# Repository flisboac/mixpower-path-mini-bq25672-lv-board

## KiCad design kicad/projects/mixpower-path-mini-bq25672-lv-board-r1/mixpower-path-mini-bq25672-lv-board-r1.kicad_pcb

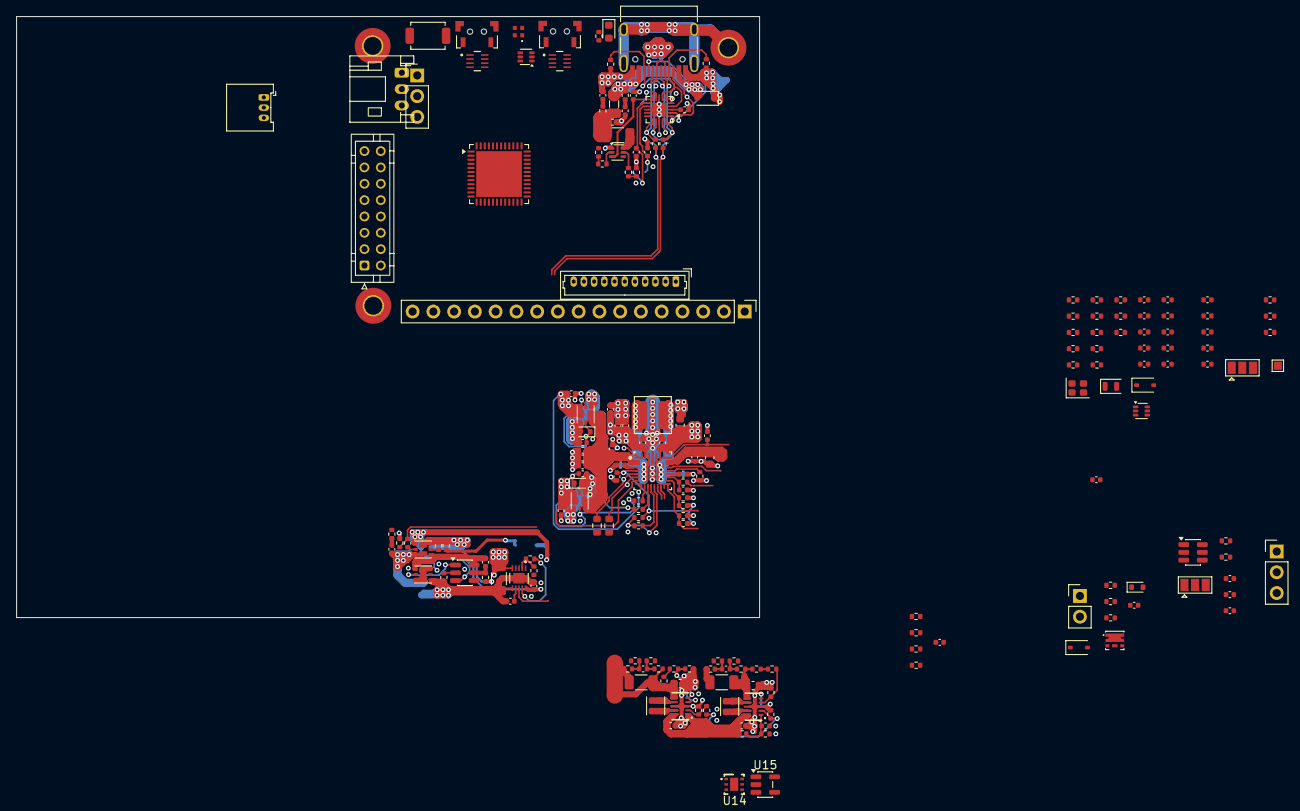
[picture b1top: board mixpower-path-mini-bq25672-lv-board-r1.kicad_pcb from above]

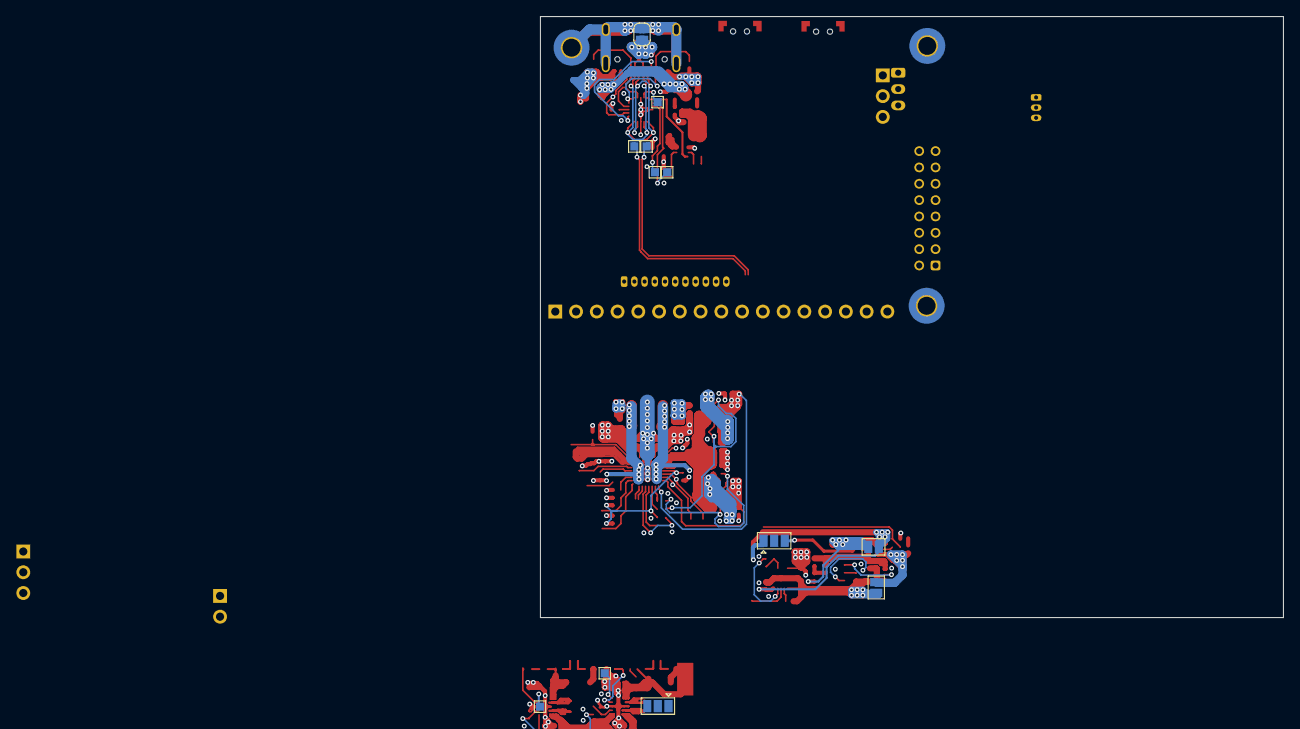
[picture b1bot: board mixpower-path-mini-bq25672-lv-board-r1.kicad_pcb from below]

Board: 4 copper layers, 90.9 x 73.6 mm, 205 parts (12 on the bottom side), 141 nets.

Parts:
C1: 1u; C_0402_1005Metric
C2: 10n; C_0402_1005Metric
C3, C4, C9, C10, C17, C18, C41, C42, C43, C44, C45, C46, C48, C49, C50, C61: 100n; C_0402_1005Metric
C5, C13, C16, C19, C20, C23, C24, C29, C30, C36, C37, C47, C51, C52, C53, C58, C60: 10u; C_0402_1005Metric
C6, C7: 330n; C_0402_1005Metric
C8, C11: 2.2u; C_0402_1005Metric
C12: 2.2u; R_0402_1005Metric
C14, C15, C21, C22: 100u; C_0402_1005Metric
C25, C26, C39, C40: 47u; C_0603_1608Metric
C27, C28, C34, C38: 1n; C_0402_1005Metric
C31, C32, C33, C35: 47n; C_0402_1005Metric
C54, C55: 7p; C_0402_1005Metric
C56, C57: 10p; C_0402_1005Metric
C59: 470p; C_0402_1005Metric
D1, D2: PESD24VV1BA; D_SOD-323
D3, D4, D5: BZX584C18; D_SOD-523
D6: RED_CHG; LED_0603_1608Metric
D7: 1N5817WS; D_SOD-323
D8: SK6805-EC14
FB1: BLM21PG300SN1D; L_0805_2012Metric
H1, H2, H3: M1; MountingHole_2.2mm_M2_Pad_TopBottom
J1: USB_C_Receptacle_HRO_TYPE-C-31-M-12
J2: BAT_HEADERS; PinHeader_1x03_P2.54mm_Vertical
J3: BATT_JST; JST_PH_S3B-PH-K_1x03_P2.00mm_Horizontal
J4: BATT_PB; Molex_PicoBlade_53048-0310_1x03_P1.25mm_Horizontal
J5: VEXT; PinHeader_1x02_P2.54mm_Vertical
J6: DATA_CONN; Molex_PicoBlade_53047-1110_1x11_P1.25mm_Vertical
J7: DATA_HEADER; PinHeader_1x17_P2.54mm_Vertical
J8: HAT; JST_PHD_B16B-PHDSS_2x08_P2.00mm_Vertical
J9: DEBUG; PinHeader_1x03_P2.54mm_Vertical
JP1: USB_GND_TO_SHIELD; SolderJumper-2_P1.3mm_Open_RoundedPad1.0x1.5mm
JP2, JP4: RTC; SolderJumper-3_P1.3mm_Open_Pad1.0x1.5mm
JP3: VCC_SEL; SolderJumper-3_P1.3mm_Open_Pad1.0x1.5mm
JP5: VDD1_SEL; SolderJumper-3_P1.3mm_Open_Pad1.0x1.5mm
JP9: SHIPFET_DIS; SolderJumper-2_P1.3mm_Open_Pad1.0x1.5mm
JP10: BPROT_DIS; SolderJumper-2_P1.3mm_Open_Pad1.0x1.5mm
L1: 1u; L_Coilcraft_XAL4020-XXX
L2, L3: 470n; L_Changjiang_FTC201612S
NT1: 3V3_TO_3V3LP; NetTie-2_SMD_Pad2.0mm
Q1, Q8: DMG1029SVQ; SOT-563
Q2, Q3, Q5, Q6: DMN3032LFDBQ; Diodes-Incorporated_U-DFN2020-6_Type-B
Q4: NTLJS17D0P03P8Z; vendor-onsemi-483av
Q7: Si1026X; SOT-563
R1, R2, R31: 5.1k; R_0402_1005Metric
R3, R4: 27; R_0402_1005Metric
R5, R6, R12, R22: 2; R_0402_1005Metric
R7, R10, R17, R27, R28: 220; R_0402_1005Metric
R8, R11, R20, R30, R77: 1M; R_0402_1005Metric
R9: 1.8k; R_1206_3216Metric
R13, R23, R34, R50, R51, R52, R53, R54, R55, R56, R57: 100k; R_0402_1005Metric
R14, R36: 100; R_0402_1005Metric
R15, R60, R76, R79: 1k; R_0402_1005Metric
R16, R19, R26, R37, R38, R41, R42, R45, R68, R69, R70, R71, R72, R73, R75: 0; R_0402_1005Metric
R18, R58, R59: 10k; R_0402_1005Metric
R21, R48, R49: 0.01; R_1206_3216Metric
R24, R25: 0; R_0603_1608Metric
R29: 2.2k; R_0402_1005Metric
R32: 30k; R_0402_1005Metric
R33: 127k; R_0402_1005Metric
R35: 3k; R_0402_1005Metric
R39, R40, R61, R64, R74: 10M; R_0402_1005Metric
R43: 806k; R_0402_1005Metric
R44, R47: 91k; R_0402_1005Metric
R46: 511k; R_0402_1005Metric
R62, R63, R65, R66, R67, R78: 4.7k; R_0402_1005Metric
SW1, SW3: TS-A002
SW2: TS-A002; SW_SPST_TS-1088-xR020
TP1: D+; TestPoint_Pad_1.0x1.0mm
TP2: D-; TestPoint_Pad_1.0x1.0mm
TP3: CC1; TestPoint_Pad_1.0x1.0mm
TP4: CC2; TestPoint_Pad_1.0x1.0mm
TP5: ~{USBC_FLT}; TestPoint_Pad_1.0x1.0mm
TP6: SOC_RST_PP; TestPoint_Pad_1.0x1.0mm
TP7: ~{5V_PG}; TestPoint_Pad_1.0x1.0mm
TP8: ~{3V3_PG}; TestPoint_Pad_1.0x1.0mm
U1: TPD8S300A; vendor-ti-RUK0020B
U2: FS312F-G; SOT-23-6
U3: MAX17055ETB; SPECIFIC_MAX17055ETB_21-100013A_T102A2&plus_1C_MXM
U4: BQ25672; vendor-ti-RQM0029A-MFG
U5, U6: TPS63802; vendor-ti-DLA0010A
U7, U8: RT9829GQW; Specific_DFN8_RT9829_RIT
U9: STM32G0B1CEU6; QFN-48-1EP_7x7mm_P0.5mm_EP5.6x5.6mm
U10: TPS22917DBV; SOT-23-6
U14: TPS7A2601; vendor-ti-DRV0006A-NoThermalVias
U15: RT9080-33GJ5; TSOT-23-5
Y1: X201232768KJD2SI; Crystal_SMD_2012-2Pin_2.0x1.2mm
Y2: X201624MKB4SI; Crystal_SMD_2016-4Pin_2.0x1.6mm

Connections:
/input-battery/BATP: JP2.3 (B), R16.1, R36.1
/input-battery/BPROT_CS: R15.1, U2.2 (CS)
/input-battery/BPROT_OC: Q3.5 (G2), U2.3 (OC)
/input-battery/BPROT_OD: Q3.2 (G1), U2.1 (OD)
/input-battery/BPROT_VCC: C9.1, R14.2, U2.5 (VCC)
/input-battery/FG_AIN: R18.2, R19.1, U3.2 (AIN)
/input-battery/FG_REG: C11.1, U3.7 (REG)
/input-battery/FG_THRM: R18.1, U3.9 (THRM)
/input-battery/SDRV: C34.1, R17.1, R20.1, U4.24 (SDRV)
/input-battery/SHIPFET_G: Q2.5 (G2), R17.2
/input-battery/VBAT_GND: C10.2, C11.2, JP10.2 (B), Q3.4 (S2), R15.2, R21.1, U3.6 (CSP), U3.11 (EPAD)
/input-battery/VBAT_GND_MID: Q3.3 (D2), Q3.6 (D1), Q3.7 (D1), Q3.8 (D2)
/input-battery/VBAT_GND_RPP: C9.2, Q2.1 (S1), Q3.1 (S1), U2.6 (GND)
/input-battery/VBAT_IN: J2.1, J3.1, J4.1, JP9.1 (A), Q2.3 (D2), Q2.8 (D2), R12.1, R13.1, R14.1, R16.2
/input-battery/VBAT_IN_GND: C8.2, J2.2, J3.2, J4.2, JP10.1 (A), Q2.6 (D1), Q2.7 (D1)
/input-battery/VBAT_IN_P: C8.1, R12.2
/input-battery/VBAT_IN_RPP_G: Q2.2 (G1), R13.2
/input-battery/~IRQ: J8.8, U3.8 (ALRT), U4.21 (~INT), U9.1 (PC13)
/input-usb/DISCH: R10.2, R11.1, U9.25 (PB13)
/input-usb/DISCH_DRAIN: Q1.6 (D1), R9.2
/input-usb/DISCH_G: Q1.2 (G1), R10.1
/input-usb/SHIELD: H1.1 (1_1), H2.1 (1_1), H3.1 (1_1), J1.S1 (SHIELD), JP1.2 (B)
/input-usb/USBC_CC1: J1.A5 (CC1), R2.1, U1.4 (C_CC1), U1.7 (RPD_G1)
/input-usb/USBC_CC2: J1.B5 (CC2), R1.1, U1.5 (C_CC2), U1.6 (RPD_G2)
/input-usb/USBC_D+: J1.A6 (D+), J1.B6 (D+), R4.1, U1.16 (D4), U1.19 (D2)
/input-usb/USBC_D-: J1.A7 (D-), J1.B7 (D-), R3.1, U1.17 (D3), U1.20 (D1)
/input-usb/USBC_SBU1: J1.A8 (SBU1), U1.1 (C_SBU1)
/input-usb/USBC_SBU2: J1.B8 (SBU2), U1.2 (C_SBU2)
/input-usb/USBC_TPS_VCC: C1.1, Q1.3 (D2), U1.10 (VPWR)
/input-usb/USBP_VBIAS: C3.1, U1.3 (VBIAS)
/input-usb/VBUS: C5.1, C18.2, FB1.2, J7.13, Q6.6 (D1), Q6.7 (D1), R6.1, R9.1, U4.8 (VAC2)
/input-usb/VBUS_USBC_IN: D1.2 (A2), FB1.1, J1.A4 (VBUS), J1.A9 (VBUS), J1.B4 (VBUS), J1.B9 (VBUS), R5.1
/input-usb/VBUS_USBC_IN_POST_P: C4.1, R6.2
/input-usb/VBUS_USBC_IN_PRE_P: C2.1, R5.2
/input-usb/VCC_DIS: R7.1, R8.1, U9.24 (PB12)
/input-usb/~FLT: TP5.1 (1_1), U1.9 (~FLT), U9.31 (PC7)
/input-vext/VEXT: C13.1, C17.1, D3.1 (K), Q4.4 (S), Q4.8 (S), Q5.6 (D1), Q5.7 (D1), U4.9 (VAC1)
/input-vext/VEXT_FLT_P: C12.1, R22.2
/input-vext/VEXT_G: D3.2 (A), Q4.3 (G), R23.1
/input-vext/VEXT_IN: D2.2 (A2), J5.1, Q4.1 (D), Q4.2 (D), Q4.5 (D), Q4.6 (D), Q4.7 (D), R22.1
/output-headers/3V3: J6.5, J7.5, J8.16, JP3.1 (A), JP5.1 (A), R49.2, R52.2
/output-headers/5V: J6.11, J7.11, J8.1, JP3.3 (B), JP5.3 (B), Q8.4 (S2), R48.2, R51.2, R77.1
/output-headers/BOOT: J6.10, J7.10, JP4.2 (C)
/output-headers/D+: J6.8, J7.8, R4.2, R24.2, TP2.1 (1_1), U9.34 (PA10/PA12)
/output-headers/D-: J6.9, J7.9, R3.2, R25.2, TP1.1 (1_1), U9.33 (PA9/PA11)
/output-headers/GP1_IRQ2: J8.12, U9.11 (PA0)
/output-headers/GP2: J8.7, U9.12 (PA1)
/output-headers/GP3: J8.14, U9.15 (PA4)
/output-headers/GP4: J8.5, U9.16 (PA5)
/output-headers/PHER2_MISO_SDA: J8.9, U9.43 (PB4)
/output-headers/PHER2_SCK: J8.6, U9.42 (PB3)
/output-headers/SWDIO: J9.1, U9.35 (PA13)
/output-headers/USER1_SCL_TX: J6.1, J7.1, J8.15, R63.2, U9.45 (PB6)
/output-headers/USER1_SDA_RX: J6.3, J7.3, J8.2, R62.2, U9.46 (PB7)
/output-headers/VDD1: C60.1, J7.12, R75.2, U10.6 (VOUT)
/output-headers/~BTN: C45.1, J6.6, J7.6, R26.2, R58.2, SW1.2, U7.3 (~SR1), U9.47 (PB8)
/output-headers/~IRQB: D7.2 (A), J6.4, J7.4, R67.2, U9.14 (PA3)
/output-headers/~RST: C46.1, J6.7, J7.7, J8.3, R59.2, SW2.2, U7.4 (~RST1), U8.3 (~SR1), U9.10 (PF2)
/power-path/BC_BATP: C35.1, R36.2, U4.18 (BATP)
/power-path/BC_BTST1: C32.1, U4.4 (BTST1)
/power-path/BC_BTST2: C33.1, U4.19 (BTST2)
/power-path/BC_D+: R24.1, U4.6 (D+)
/power-path/BC_D-: R25.1, U4.7 (D-)
/power-path/BC_ILIM: R33.1, R34.2, U4.17 (ILIM_HIZ)
/power-path/BC_PROG: R35.2, U4.20 (PROG)
/power-path/TS: J2.3, J3.3, J4.3, R19.2, R31.1, R32.2, U4.16 (TS)
/power-path/VAC1_MID: C27.1, D4.2 (A), Q5.1 (S1), Q5.4 (S2)
/power-path/VAC2_MID: C28.2, D5.2 (A), Q6.1 (S1), Q6.4 (S2)
/power-path/VBAT: C10.1, C22.1, C26.1, J7.16, JP2.1 (A), JP9.2 (B), Q2.4 (S2), U3.10 (BATT), U4.22 (BAT), U4.23 (BAT)
/power-path/VIN1_ACDRV_G: R27.2, U4.11 (ACDRV1)
/power-path/VIN1_G: C27.2, D4.1 (K), Q5.2 (G1), Q5.5 (G2), R27.1
/power-path/VIN2_ACDRV_G: R28.2, U4.10 (ACDRV2)
/power-path/VIN2_G: C28.1, D5.1 (K), Q6.2 (G1), Q6.5 (G2), R28.1
/power-path/VOTG: C15.1, C20.1, C24.1, C30.1, J7.15, U4.29 (PMID)
/power-path/VREGNLP: C16.1, R29.2, R30.2, R31.2, R33.2, U4.5 (REGN)
/power-path/VSEL: C14.1, C19.1, C23.1, C29.1, Q5.3 (D2), Q5.8 (D2), Q6.3 (D2), Q6.8 (D2), U4.2 (VBUS), U4.3 (VBUS)
/power-path/VSWN_SW1: C32.2, L1.1, U4.28 (SW1)
/power-path/VSWN_SW2: C33.2, L1.2, U4.26 (SW2)
/power-path/VSYS: C21.1, C25.1, C36.1, C37.1, J7.14, R39.2, U4.25 (SYS), U5.10 (VIN), U6.1 (EN), U6.10 (VIN)
/power-path/~BC_QON: R26.1, U4.12 (~QON)
/power-path/~CE: C31.1, R30.1, U4.13 (~CE), U9.39 (PD1)
/power-path/~STAT: D6.1 (K), U4.1 (STAT)
/soc-control/3V3LP: C50.1, C53.1, NT1.1, Q1.4 (S2), U9.6 (VDD)
/soc-control/5V_EN: R37.2, U9.41 (PD3)
/soc-control/BOOT: C47.1, JP4.1 (A), R60.2, R72.2, SW3.2
/soc-control/FRSTX1: Q7.2 (G), R61.1, U9.26 (PB14)
/soc-control/FRSTX2: Q7.5 (G), R64.1, U9.30 (PC6)
/soc-control/IRQB_TX: D7.1 (K), U9.13 (PA2)
/soc-control/OSC32_IN: R68.2, U9.2 (PC14)
/soc-control/OSC32_OUT: R69.2, U9.3 (PC15)
/soc-control/OSC_IN: R70.1, U9.8 (PF0)
/soc-control/OSC_OUT: R71.2, U9.9 (PF1)
/soc-control/PHER1_SCL: J8.13, R66.2, U3.3 (SCL), U4.14 (SCL), U9.18 (PA7)
/soc-control/PHER1_SDA: J8.4, R65.2, U3.4 (SDA), U4.15 (SDA), U9.17 (PA6)
/soc-control/PHER2_MOSI_SCL: J8.11, R73.1, U9.44 (PB5)
/soc-control/PHER2_RGB_CS: Q8.2 (G1), R78.1, U9.37 (PA15)
/soc-control/PHER2_RGB_DO: Q8.1 (S1), R73.2, R78.2
/soc-control/SNS_3V3_N: C42.1, R52.1, R56.1, U9.20 (PB1)
/soc-control/SNS_3V3_P: C42.2, R53.1, R57.1, U9.19 (PB0)
/soc-control/SNS_5V_N: C41.2, R51.1, R55.1, U9.22 (PB10)
/soc-control/SNS_5V_P: C41.1, R50.1, R54.1, U9.21 (PB2)
/soc-control/SWCLK: J9.3, R72.1, U9.36 (PA14)
/soc-control/SWREG_MODE: R38.2, R40.2, U5.2 (MODE), U9.40 (PD2)
/soc-control/USBC_CC1: C6.1, Q7.6 (D), TP3.1 (1_1), U1.12 (CC1), U9.28 (PA8), U9.29 (PA9/UCPD1_DBCC1)
/soc-control/USBC_CC2: C7.1, Q7.3 (D), TP4.1 (1_1), U1.11 (CC2), U9.27 (PB15), U9.32 (PA10/UCPD1_DBCC2)
/soc-control/VBAT: C48.1, C51.1, JP2.2 (C), U9.4 (VBAT)
/soc-control/VDD1_EN: R74.1, U9.48 (PB9), U10.3 (ON)
/soc-control/VREF: C49.1, C52.1, U9.5 (VREF+)
/soc-control/~PHER2_RGB_EN: R76.2, U9.38 (PD0)
/soc-vreg/3V3_PRE: C40.1, NT1.2, R45.2, R49.1, R53.2, U6.6 (VOUT)
/soc-vreg/5V_PRE: C39.1, R42.2, R48.1, R50.2, U5.6 (VOUT)
/soc-vreg/VSWN_3V3_L1: L3.1, U6.9 (L1)
/soc-vreg/VSWN_3V3_L2: L3.2, U6.7 (L2)
/soc-vreg/VSWN_5V_L1: L2.1, U5.9 (L1)
/soc-vreg/VSWN_5V_L2: L2.2, U5.7 (L2)
/soc-vreg/VSWREG_3V3_FB: R46.1, R47.2, U6.4 (FB)
/soc-vreg/VSWREG_3V3_MODE: R38.1, R41.2, U6.2 (MODE)
/soc-vreg/VSWREG_3V3_PG: TP8.1 (1_1), U6.5 (PG)
/soc-vreg/VSWREG_5V_EN: C38.1, R37.1, R39.1, U5.1 (EN)
/soc-vreg/VSWREG_5V_FB: R43.1, R44.2, U5.4 (FB)
/soc-vreg/VSWREG_5V_PG: TP7.1 (1_1), U5.5 (PG)
/soc-vreg/~SNS_EN: R54.2, R55.2, R56.2, R57.2, U9.23 (PB11)
/util-buttons/SRST_BOOT_RST1: JP4.3 (B), U8.4 (~RST1)
/util-buttons/SRST_BOOT_RST2: R60.1, U8.1 (RST2)
/util-buttons/SRST_RST_RST2: TP6.1 (1_1), U7.1 (RST2)
/util-buttons/VPULLUP: C43.1, C44.1, JP3.2 (C), R58.1, R59.1, R62.1, R63.1, R65.1, R66.1, R67.1, SW3.1, U7.8 (VCC), U8.8 (VCC)
/util-rgb/EN_G: Q8.5 (G2), R76.1, R77.2
/util-rgb/VIN_RGB_LP: C61.1, D8.1 (VDD), Q8.3 (D2), R79.1
/vpath-vdd1/VDD1_CT_G: C59.2, U10.4 (CT)
/vpath-vdd1/VDD1_IN: C58.1, C59.1, JP5.2 (C), U10.1 (VIN)
/vpath-vdd1/VDD1_QOD_G: R75.1, U10.5 (QOD)
GND: C1.2, C2.2, C3.2, C4.2, C5.2, C6.2, C7.2, C12.2, C13.2, C14.2, C15.2, C16.2, C17.2, C18.1, C19.2, C20.2, C21.2, C22.2, C23.2, C24.2, C25.2, C26.2, C29.2, C30.2, C31.2, C34.2, C35.2, C36.2, C37.2, C38.2, C39.2, C40.2, C43.2, C44.2, C45.2, C46.2, C47.2, C48.2, C49.2, C50.2, C51.2, C52.2, C53.2, C54.1, C55.2, C56.1, C57.2, C58.2, C60.2, C61.2, D1.1 (A1), D2.1 (A1), D8.3 (GND), J1.A1 (GND), J1.A12 (GND), J1.B1 (GND), J1.B12 (GND), J5.2, J6.2, J7.2, J7.17, J8.10, J9.2, JP1.1 (A), Q1.1 (S1), Q7.1 (S), Q7.4 (S), R1.2, R2.2, R8.2, R11.2, R20.2, R21.2, R23.2, R32.1, R34.1, R35.1, R40.1, R41.1, R44.1, R47.1, R61.2, R64.2, R74.2, SW1.1, SW2.1, U1.8 (GND), U1.13 (GND), U1.18 (GND), U1.21 (GND), U3.5 (CSN), U4.27 (GND), U5.3 (AGND), U5.8 (GND), U6.3 (AGND), U6.8 (GND), U7.2 (VSS), U7.5 (DSR), U7.7 (~SR0), U8.2 (VSS), U8.5 (DSR), U8.7 (~SR0), U9.7 (VSS), U9.49 (VSS), U10.2 (GND), Y2.2 (G), Y2.4 (G)
unnamed: C54.2, R68.1, Y1.2
unnamed: C55.1, R69.1, Y1.1
unnamed: C56.2, R70.2, Y2.1
unnamed: C57.1, R71.1, Y2.3
unnamed: D6.2 (A), R29.1
unnamed: D8.4 (DI), Q8.6 (D1), R79.2
unnamed: Q1.5 (G2), R7.2
unnamed: R42.1, R43.2
unnamed: R45.1, R46.2

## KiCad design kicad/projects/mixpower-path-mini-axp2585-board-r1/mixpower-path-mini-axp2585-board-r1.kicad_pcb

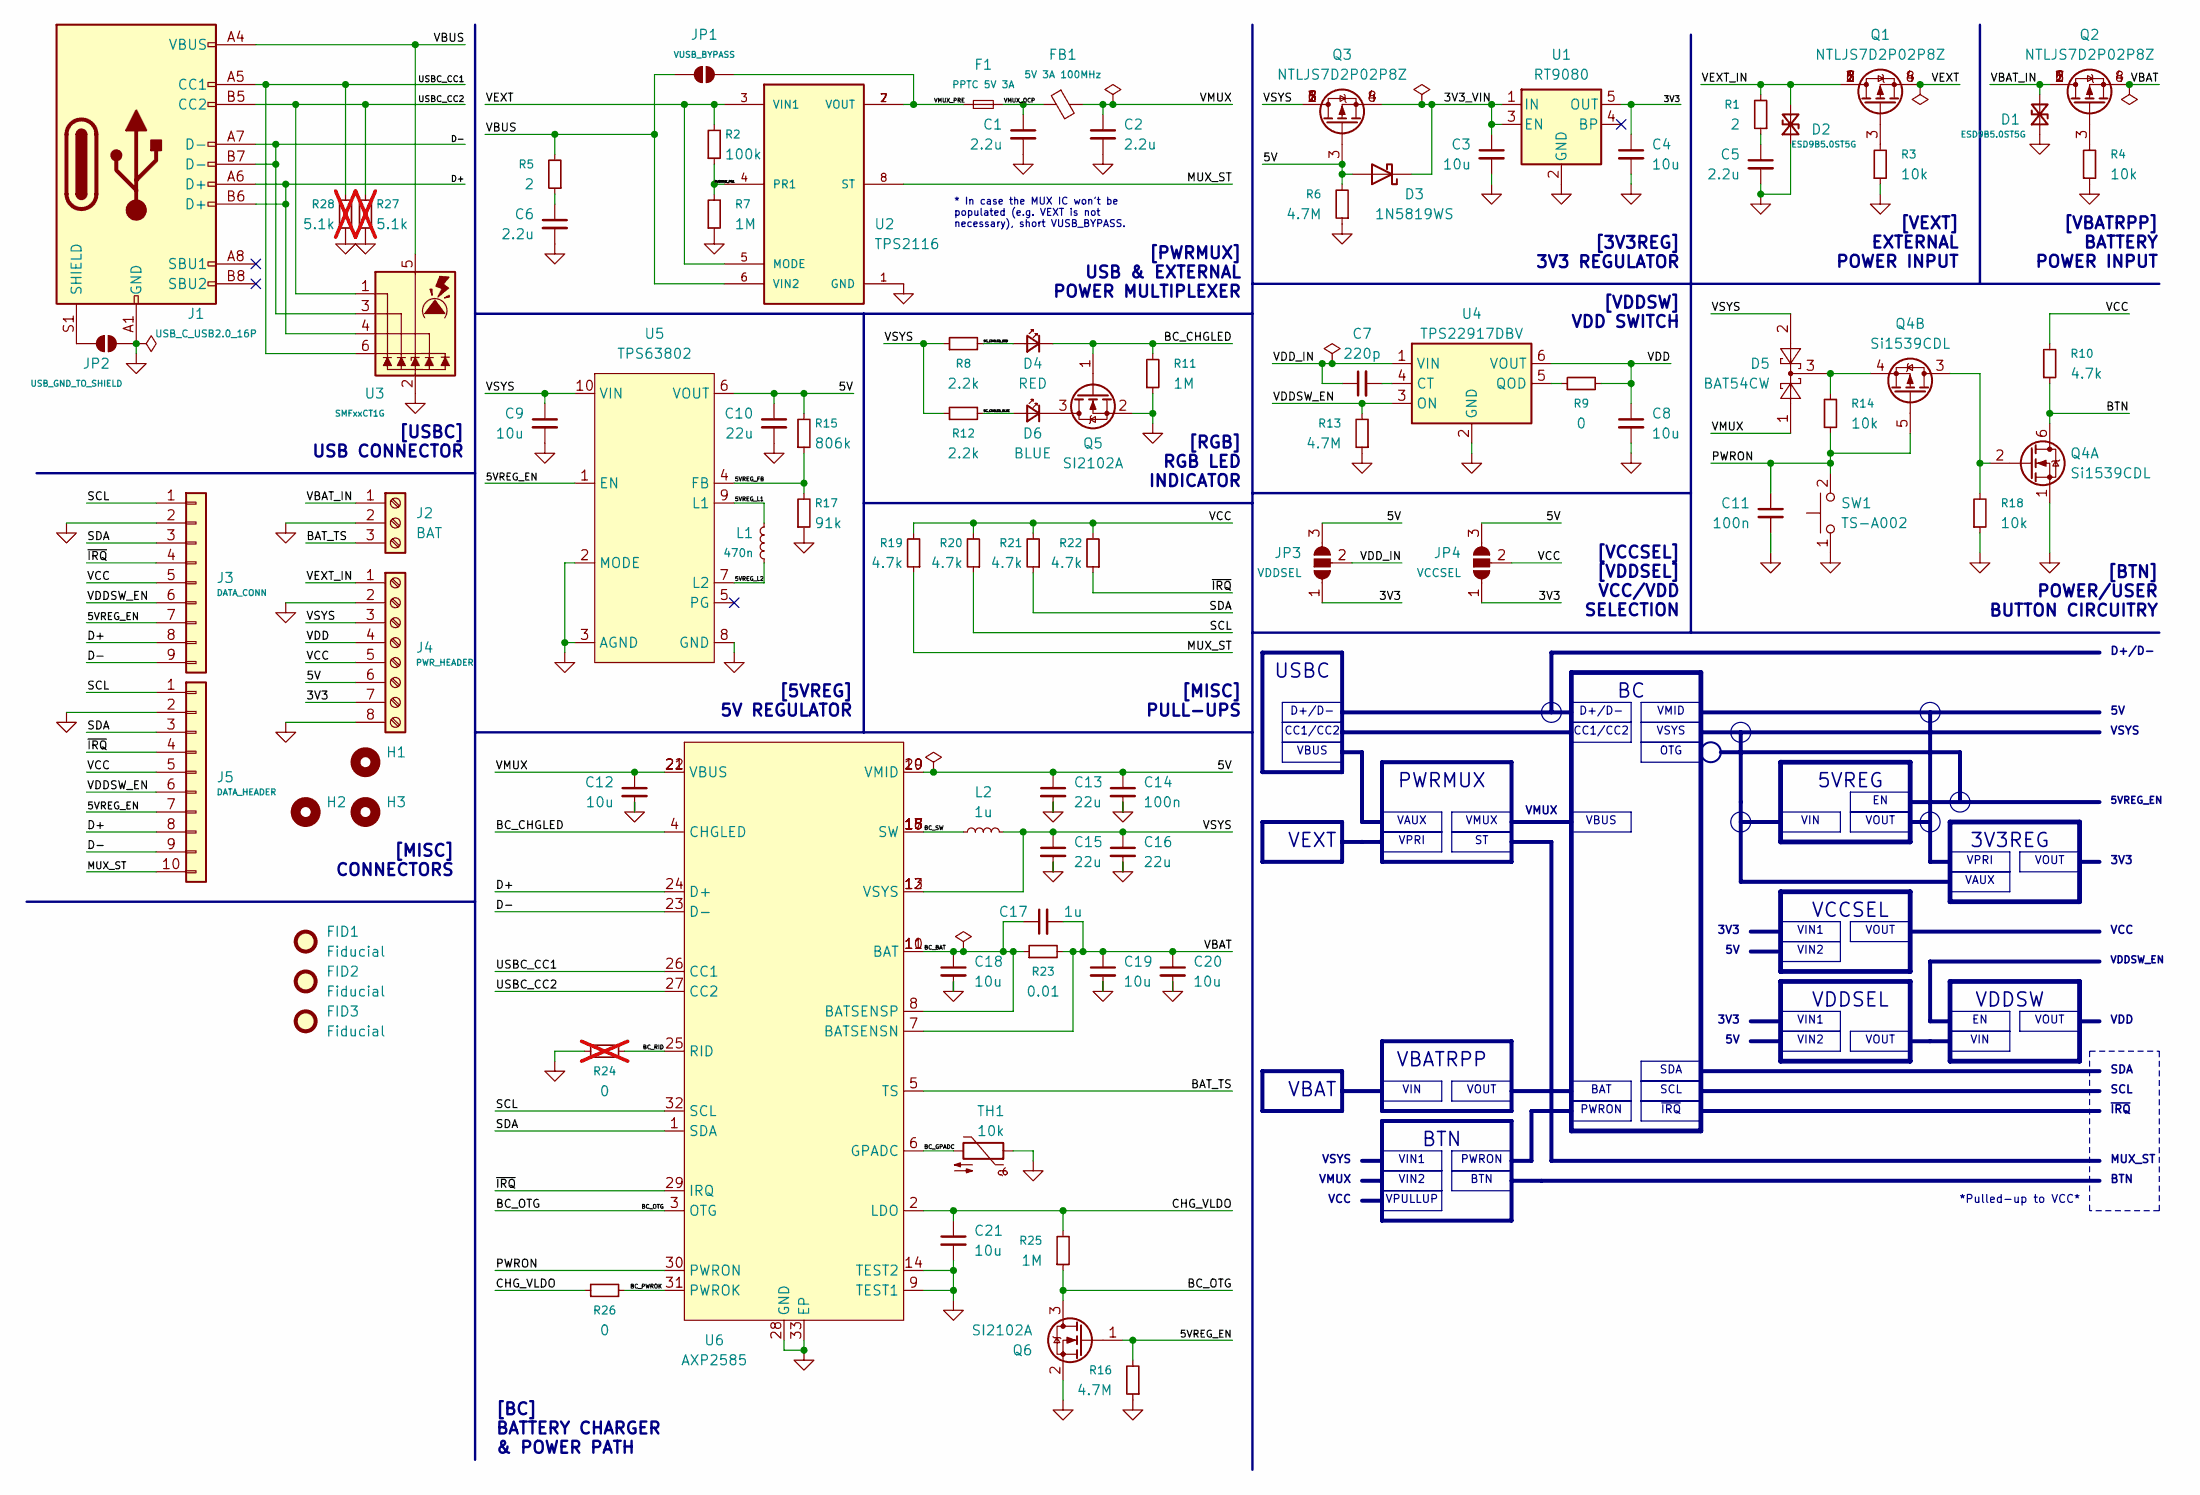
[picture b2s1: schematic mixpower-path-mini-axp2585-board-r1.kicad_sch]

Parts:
C1, C2, C5, C6: 2.2u; C_0402_1005Metric
C3, C4, C8, C12, C18, C19, C20, C21: 10u; C_0402_1005Metric
C7: 220p; C_0402_1005Metric
C9: 10u; C_0603_1608Metric
C10, C13, C15, C16: 22u; C_0603_1608Metric
C11, C14: 100n; C_0402_1005Metric
C17: 1u; C_0402_1005Metric
D1, D2: ESD9B5.0ST5G; D_SOD-923
D3: 1N5819WS; D_SOD-323
D4: RED; LED_0603_1608Metric
D5: BAT54CW; SOT-323_SC-70
D6: BLUE; LED_0603_1608Metric
F1: PPTC 5V 3A; Fuse_1210_3225Metric
FB1: 5V 3A 100MHz; L_1210_3225Metric
FID1, FID2, FID3: Fiducial; Fiducial_0.5mm_Mask1mm
H1, H2, H3: MountingHole; MountingHole_2.2mm_M2
J1: USB_C_USB2.0_16P; USB_C_Receptacle_HRO_TYPE-C-31-M-12
J2: BAT; JST_PH_S3B-PH-K_1x03_P2.00mm_Horizontal
J3: DATA_CONN; JST_ZH_B9B-ZR_1x09_P1.50mm_Vertical
J4: PWR_HEADER; PinHeader_1x08_P2.54mm_Vertical
J5: DATA_HEADER; PinHeader_1x10_P2.54mm_Vertical
JP1: VUSB_BYPASS; SolderJumper-2_P1.3mm_Open_RoundedPad1.0x1.5mm
JP2: USB_GND_TO_SHIELD; SolderJumper-2_P1.3mm_Open_RoundedPad1.0x1.5mm
JP3: VDDSEL; SolderJumper-3_P1.3mm_Open_RoundedPad1.0x1.5mm
JP4: VCCSEL; SolderJumper-3_P1.3mm_Open_RoundedPad1.0x1.5mm
L1: 470n; L_Coilcraft_XxL4020
L2: 1u; L_Coilcraft_XAL4020-XXX
Q1, Q2, Q3: NTLJS7D2P02P8Z; vendor-onsemi-483av
Q4: Si1539CDL; SOT-363_SC-70-6
Q5, Q6: SI2102A; SOT-323_SC-70
R1, R5: 2; R_0402_1005Metric
R2: 100k; R_0402_1005Metric
R3, R4, R14, R18: 10k; R_0402_1005Metric
R6, R13, R16: 4.7M; R_0402_1005Metric
R7, R11, R25: 1M; R_0402_1005Metric
R8, R12: 2.2k; R_0402_1005Metric
R9, R26: 0; R_0402_1005Metric
R10, R19, R20, R21, R22: 4.7k; R_0402_1005Metric
R15: 806k; R_0402_1005Metric
R17: 91k; R_0402_1005Metric
R23: 0.01; R_1210_3225Metric
R24: 0; R_0402_1005Metric; not fitted
R27, R28: 5.1k; R_0402_1005Metric; not fitted
SW1: TS-A002
TH1: 10k; R_0603_1608Metric
U1: RT9080; SOT-23-5
U2: TPS2116
U3: SMFxxCT1G; SOT-363_SC-70-6
U4: TPS22917DBV; SOT-23-6
U5: TPS63802; vendor-ti-DLA0010A
U6: AXP2585; QFN-32-1EP_5x5mm_P0.4mm_EP3x3mm; LCSC C20199912

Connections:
/3V3: C4.1, J4.7, JP3.1 (A), JP4.1 (A), U1.5 (OUT)
/3V3_VIN: C3.1, D3.1 (K), Q3.4 (S), Q3.8 (S), U1.1 (IN), U1.3 (EN)
/5V: C10.1, C13.1, C14.1, D3.2 (A), J4.6, JP3.3 (B), JP4.3 (B), Q3.3 (G), R6.2, R15.2, U5.6 (VOUT), U6.19 (VMID), U6.20 (VMID)
/5VREG_EN: J2.7, J3.7, J5.7, Q6.1 (G), R16.2, U5.1 (EN)
/5VREG_FB: R15.1, R17.2, U5.4 (FB)
/5VREG_L1: L1.1, U5.9 (L1)
/5VREG_L2: L1.2, U5.7 (L2)
/BC_BAT: C17.1, C18.1, R23.1, U6.8 (BATSENSP), U6.10 (BAT), U6.11 (BAT)
/BC_CHGLED: D4.1 (K), Q5.1 (G), R11.2, U6.4 (CHGLED)
/BC_CHGLED_BLUE: D6.2 (A), R12.2
/BC_CHGLED_RED: D4.2 (A), R8.2
/BC_GPADC: TH1.2, U6.6 (GPADC)
/BC_OTG: Q6.3 (D), R25.1, U6.3 (OTG)
/BC_PWROK: R26.2, U6.31 (PWROK)
/BC_RID: R24.2, U6.25 (RID)
/BC_SW: L2.1, U6.15 (SW), U6.16 (SW), U6.17 (SW), U6.18 (SW)
/BTN: Q4.6 (D1), R10.1
/CHG_VLDO: C21.1, R25.2, R26.1, U6.2 (LDO)
/D+: J1.A6 (D+), J1.B6 (D+), J2.8, J3.8, J5.8, U3.4 (I/O3), U6.24 (D+)
/D-: J1.A7 (D-), J1.B7 (D-), J2.9, J3.9, J5.9, U3.3 (I/O2), U6.23 (D-)
/MUX_ST: J2.10, J5.10, R19.1, U2.8 (ST)
/PWRMUX_PR1: R2.1, R7.2, U2.4 (PR1)
/PWRON: C11.1, Q4.5 (G2), R14.1, SW1.2, U6.30 (PWRON)
/USBC_CC1: J1.A5 (CC1), R28.2, U3.6 (I/O4), U6.26 (CC1)
/USBC_CC2: J1.B5 (CC2), R27.2, U3.1 (I/O1), U6.27 (CC2)
/VBAT: C17.2, C19.1, C20.1, Q2.4 (S), Q2.8 (S), R23.2, U6.7 (BATSENSN)
/VBUS: J1.A4 (VBUS), J1.A9 (VBUS), J1.B4 (VBUS), J1.B9 (VBUS), JP1.2 (B), R5.2, U2.6 (VIN2), U3.5 (I/O5)
/VCC: J2.5, J3.5, J4.5, J5.5, JP4.2 (C), R10.2, R19.2, R20.2, R21.2, R22.2
/VDD: C8.1, J4.4, R9.2, U4.6 (VOUT)
/VDDSW_EN: J2.6, J3.6, J5.6, R13.2, U4.3 (ON)
/VDD_IN: C7.1, JP3.2 (C), U4.1 (VIN)
/VEXT: Q1.4 (S), Q1.8 (S), R2.2, U2.3 (VIN1), U2.5 (MODE)
/VEXT_IN: D2.2 (A2), J4.1, Q1.1 (D), Q1.2 (D), Q1.5 (D), Q1.6 (D), Q1.7 (D), R1.2
/VMUX: C2.1, C12.1, D5.1 (A1), FB1.2, U6.21 (VBUS), U6.22 (VBUS)
/VMUX_OCP: C1.1, F1.2, FB1.1
/VMUX_PRE: F1.1, JP1.1 (A), U2.2 (VOUT), U2.7 (VOUT)
/VSYS: C9.1, C15.1, C16.1, D5.2 (A2), J4.3, L2.2, Q3.1 (D), Q3.2 (D), Q3.5 (D), Q3.6 (D), Q3.7 (D), R8.1, R12.1, U5.10 (VIN), U6.12 (VSYS), U6.13 (VSYS)
/~IRQ: J2.4, J3.4, J5.4, R22.1, U6.29 (IRQ)
GND: C1.2, C2.2, C3.2, C4.2, C5.2, C6.2, C8.2, C9.2, C10.2, C11.2, C12.2, C13.2, C14.2, C15.2, C16.2, C18.2, C19.2, C20.2, C21.2, D1.1 (A1), D2.1 (A1), J1.A1 (GND), J1.A12 (GND), J1.B1 (GND), J1.B12 (GND), J2.2, J3.2, J4.2, J4.8, J5.2, JP2.1 (A), Q4.1 (S1), Q5.2 (S), Q6.2 (S), R3.1, R4.1, R6.1, R7.1, R11.1, R13.1, R16.1, R17.1, R18.1, R24.1, R27.1, R28.1, SW1.1, TH1.1, U1.2 (GND), U2.1 (GND), U3.2 (GND), U4.2 (GND), U5.2 (MODE), U5.3 (AGND), U5.8 (GND), U6.9 (TEST1), U6.14 (TEST2), U6.28 (GND), U6.33 (EP); also elsewhere on the board
unnamed: C5.1, R1.1
unnamed: C6.1, R5.1
unnamed: D5.3 (K), Q4.4 (S2), R14.2
unnamed: D6.1 (K), Q5.3 (D)
unnamed: J1.S1 (SHIELD), JP2.2 (B)
unnamed: Q1.3 (G), R3.2
unnamed: Q2.3 (G), R4.2
unnamed: Q4.2 (G1), Q4.3 (D2), R18.2
unnamed: C7.2, U4.4 (CT)
unnamed: R9.1, U4.5 (QOD)

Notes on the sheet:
3V3
VIN2
VBUS
~{IRQ}
VEXT
SDA
BTN
*Pulled-up to VCC*
VMUX
[VCCSEL] [VDDSEL] VCC/VDD SELECTION
VIN1
VOUT
VSYS
VBAT
5VREG
VAUX
[BTN] POWER/USER BUTTON CIRCUITRY
PWRMUX
VIN
SCL
CC1/CC2
VDD
PWRON
VCC
D+/D-
VDDSW_EN
* In case the MUX IC won't be populated (e.g. VEXT is not necessary), short VUSB_BYPASS.
VPRI
[VEXT] EXTERNAL POWER INPUT
[PWRMUX] USB & EXTERNAL POWER MULTIPLEXER
[USBC] USB CONNECTOR
3V3REG
VDDSW
~{IRQ}
5VREG_EN
[5VREG] 5V REGULATOR
VDDSEL
VBATRPP
USBC
MUX_ST

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
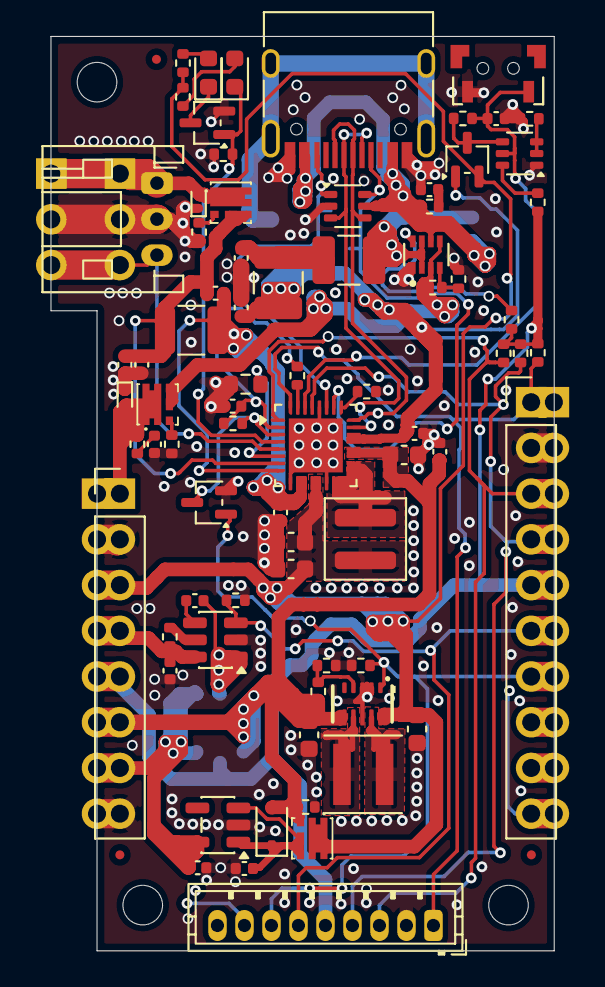
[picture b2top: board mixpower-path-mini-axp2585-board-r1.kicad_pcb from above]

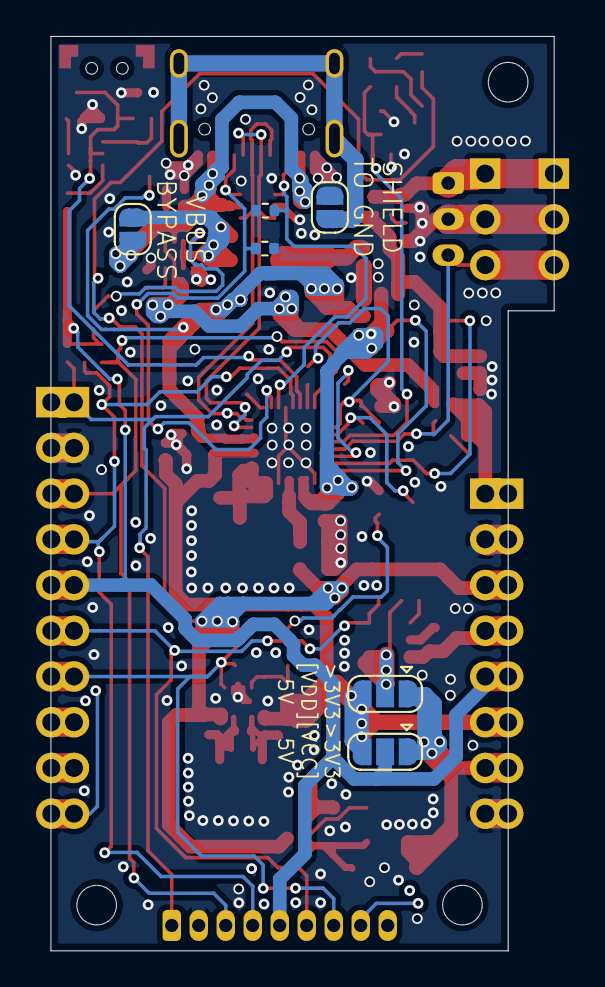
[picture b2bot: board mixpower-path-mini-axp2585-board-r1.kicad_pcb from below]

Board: 4 copper layers, 28.0 x 50.8 mm, 89 parts (6 on the bottom side), 53 nets.

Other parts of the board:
J2#2: BAT; JST_PH_S3B-PH-K_1x03_P2.00mm_Horizontal

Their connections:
GND: J2#2.2; also elsewhere on the board

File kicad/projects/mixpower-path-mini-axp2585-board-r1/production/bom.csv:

Designator,Footprint,Quantity,Value,LCSC Part #
"C1, C2, C5, C6",0402,4,2.2u,
"C10, C13, C15, C16",0603,4,22u,
"C11, C14",0402,2,100n,
"C12, C18, C19, C20, C21, C3, C4, C8",0402,8,10u,
C17,0402,1,1u,
C7,0402,1,220p,
C9,0603,1,10u,
"D1, D2",D_SOD-923,2,ESD9B5.0ST5G,
D3,D_SOD-323,1,1N5819WS,
D4,0603,1,RED,
D5,SOT-323_SC-70,1,BAT54CW,
D6,0603,1,BLUE,
F1,1210,1,PPTC 5V 3A,
FB1,1210,1,5V 3A 100MHz,
J1,USB_C_Receptacle_HRO_TYPE-C-31-M-12,1,USB_C_USB2.0_16P,
"J2_2, J5",PinHeader_1x10_P2.54mm_Vertical,2,DATA_HEADER,
J2,JST_PH_S3B-PH-K_1x03_P2.00mm_Horizontal,1,BAT,
J3,JST_ZH_B9B-ZR_1x09_P1.50mm_Vertical,1,DATA_CONN,
J4,PinHeader_1x08_P2.54mm_Vertical,1,PWR_HEADER,
L1,L_Coilcraft_XxL4020,1,470n,
L2,L_Coilcraft_XAL4020-XXX,1,1u,
"Q1, Q2, Q3",vendor-onsemi-483av,3,NTLJS7D2P02P8Z,
Q4,SOT-363_SC-70-6,1,Si1539CDL,
"Q5, Q6",SOT-323_SC-70,2,SI2102A,
"R1, R5",0402,2,2,
"R10, R19, R20, R21, R22",0402,5,4.7k,
"R11, R25, R7",0402,3,1M,
"R12, R8",0402,2,2.2k,
"R13, R16, R6",0402,3,4.7M,
"R14, R18, R3, R4",0402,4,10k,
R15,0402,1,806k,
R17,0402,1,91k,
R2,0402,1,100k,
R23,1210,1,0.01,
"R24, R26, R9",0402,3,0,
SW1,TS-A002,1,TS-A002,
TH1,0603,1,10k,
U1,SOT-23-5,1,RT9080,
U2,TPS2116,1,TPS2116,
U3,SOT-363_SC-70-6,1,SMFxxCT1G,
U4,SOT-23-6,1,TPS22917DBV,
U5,vendor-ti-DLA0010A,1,TPS63802,
U6,QFN-32-1EP_5x5mm_P0.4mm_EP3x3mm,1,AXP2585,C20199912

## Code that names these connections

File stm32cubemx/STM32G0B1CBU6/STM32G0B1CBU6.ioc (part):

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Mcu.Name=STM32G0B1C(B-C-E)Ux
Mcu.Package=UFQFPN48
Mcu.UserName=STM32G0B1CEUx
PA0.GPIOParameters=GPIO_Label
PA0.GPIO_Label=PHER2__GP1__IRQ2__SYS_WKUP2
PA0.Signal=SharedStack_PA0
PA0.Stacked=true
PA1.GPIOParameters=GPIO_Label
PA1.GPIO_Label=PHER2__GP2
PA1.Signal=GPIO_Output
PA10.GPIOParameters=GPIO_Label
PA10.GPIO_Label=USBC__UCPD1_DBCC2
PA10.Mode=EnableDeadBattery
PA10.Signal=UCPD1_DBCC2
PA11\ [PA9].GPIOParameters=GPIO_Label
PA11\ [PA9].GPIO_Label=USBC__USB_DM
PA11\ [PA9].Mode=Device
PA11\ [PA9].Signal=USB_DM
PA12\ [PA10].GPIOParameters=GPIO_Label
PA12\ [PA10].GPIO_Label=USBC__USB_DP
PA12\ [PA10].Mode=Device
PA12\ [PA10].Signal=USB_DP
PA13.GPIOParameters=GPIO_Label
PA13.GPIO_Label=MCU__SYS_SWDIO
PA13.Mode=Serial_Wire
PA13.Signal=SYS_SWDIO
PA14-BOOT0.GPIOParameters=GPIO_Label
PA14-BOOT0.GPIO_Label=MCU__SYS_SWCLK__BOOT0
PA14-BOOT0.Mode=Serial_Wire
PA14-BOOT0.Signal=SYS_SWCLK
PA15.GPIOParameters=GPIO_Label
PA15.GPIO_Label=PHER2__RGB_CS
PA15.Signal=GPIO_Analog
PA2.GPIOParameters=GPIO_Label
PA2.GPIO_Label=IRQB__LPUART1_TX__SYS_WKUP4
PA2.Signal=SharedStack_PA2
PA2.Stacked=true
PA3.GPIOParameters=GPIO_Label
PA3.GPIO_Label=IRQB__LPUART1_RX
PA3.Mode=Asynchronous
PA3.Signal=LPUART1_RX
PA4.GPIOParameters=GPIO_Label
PA4.GPIO_Label=PHER2__GP3__ADC1_IN4__DAC1_OUT1
PA4.Signal=SharedStack_PA4
PA4.Stacked=true
PA5.GPIOParameters=GPIO_Label
PA5.GPIO_Label=PHER2__GP4__ADC1_IN5__DAC1_OUT2
PA5.Signal=SharedStack_PA5
PA5.Stacked=true
PA6.GPIOParameters=GPIO_Label
PA6.GPIO_Label=PHER1__I2C2_SDA
PA6.Mode=I2C
PA6.Signal=I2C2_SDA
PA7.GPIOParameters=GPIO_Label
PA7.GPIO_Label=PHER1__I2C2_SCL
PA7.Mode=I2C
PA7.Signal=I2C2_SCL
PA8.GPIOParameters=GPIO_Label
PA8.GPIO_Label=USBC__UCPD1_CC1
PA8.Mode=Dual_Role_AllSignals
PA8.Signal=UCPD1_CC1
PA9.GPIOParameters=GPIO_Label
PA9.GPIO_Label=USBC__UCPD1_DBCC1
PA9.Mode=EnableDeadBattery
PA9.Signal=UCPD1_DBCC1
PB0.GPIOParameters=GPIO_Label
PB0.GPIO_Label=ADC__SNS_3V3_P
PB0.Mode=IN8
PB0.Signal=ADC1_IN8
PB1.GPIOParameters=GPIO_Label
PB1.GPIO_Label=ADC__SNS_3V3_N
PB1.Mode=IN9
PB1.Signal=ADC1_IN9
PB10.GPIOParameters=GPIO_Label
PB10.GPIO_Label=ADC__SNS_5V_N
PB10.Mode=IN11
PB10.Signal=ADC1_IN11
PB11.GPIOParameters=GPIO_Label
PB11.GPIO_Label=ADC__SNS_EN
PB11.Signal=GPIO_Output
PB12.GPIOParameters=GPIO_Label
PB12.GPIO_Label=USBC__VCC_DIS
PB12.Signal=GPIO_Output
PB13.GPIOParameters=GPIO_Label
PB13.GPIO_Label=USBC__DISCH
PB13.Signal=GPIO_Input
PB14.GPIOParameters=GPIO_Label
PB14.GPIO_Label=USBC__UCPD1_FRSTX1
PB14.Mode=FRSTX_CC2
PB14.Signal=UCPD1_FRSTX1
PB15.GPIOParameters=GPIO_Label
PB15.GPIO_Label=USBC__UCPD1_CC2
PB15.Mode=Dual_Role_AllSignals
PB15.Signal=UCPD1_CC2
PB2.GPIOParameters=GPIO_Label
PB2.GPIO_Label=ADC__SNS_5V_P
PB2.Mode=IN10
PB2.Signal=ADC1_IN10
PB3.GPIOParameters=GPIO_Label
PB3.GPIO_Label=PHER2__SPI1_SCK__COMP2_INM
PB3.Mode=Full_Duplex_Master
PB3.Signal=SPI1_SCK
PB4.GPIOParameters=GPIO_Label
PB4.GPIO_Label=PHER2__SPI1_MISO__COMP2_INP
PB4.Mode=Full_Duplex_Master
PB4.Signal=SPI1_MISO
PB5.GPIOParameters=GPIO_Label
PB5.GPIO_Label=PHER2__SPI1_MOSI__COMP2_OUT
PB5.Mode=Full_Duplex_Master
PB5.Signal=SPI1_MOSI
PB5.Stacked=true
PB6.GPIOParameters=GPIO_Label
PB6.GPIO_Label=USER1__I2C1_SCL__LPUART2_TX
PB6.Signal=SharedStack_PB6
PB6.Stacked=true
PB7.GPIOParameters=GPIO_Label
PB7.GPIO_Label=USER1__I2C1_SDA__LPUART2_RX
PB7.Signal=SharedStack_PB7
PB7.Stacked=true
PB8.GPIOParameters=GPIO_Label
PB8.GPIO_Label=USER1__BTN0
PB8.Signal=GPIO_Input
PB9.GPIOParameters=GPIO_Label
PB9.GPIO_Label=PMIC__VDD1_EN
PB9.Signal=GPIO_Analog
PC13.GPIOParameters=GPIO_Label
PC13.GPIO_Label=PHER1__IRQ1__SYS_WKUP1
PC13.Signal=SharedStack_PC13
PC13.Stacked=true
PC14-OSC32_IN\ (PC14).GPIOParameters=GPIO_Label
PC14-OSC32_IN\ (PC14).GPIO_Label=MCU__RCC_OSC32_IN
PC14-OSC32_IN\ (PC14).Mode=LSE-External-Oscillator
PC14-OSC32_IN\ (PC14).Signal=RCC_OSC32_IN
PC15-OSC32_OUT\ (PC15).GPIOParameters=GPIO_Label
PC15-OSC32_OUT\ (PC15).GPIO_Label=MCU__RCC_OSC32_OUT
PC15-OSC32_OUT\ (PC15).Mode=LSE-External-Oscillator
PC15-OSC32_OUT\ (PC15).Signal=RCC_OSC32_OUT
PC6.GPIOParameters=GPIO_Label
PC6.GPIO_Label=USBC__UCPD1_FRSTX2
PC6.Mode=FRSTX_CC2
PC6.Signal=UCPD1_FRSTX2
PC7.GPIOParameters=GPIO_Label
PC7.GPIO_Label=USBC__FAULT
PC7.Signal=GPIO_Input
PD0.GPIOParameters=GPIO_Label
PD0.GPIO_Label=PHER2__RGB_EN
PD0.Signal=GPIO_Output
PD1.GPIOParameters=GPIO_Label
PD1.GPIO_Label=PMIC__BC_CHGEN
PD1.Signal=GPIO_Output
PD2.GPIOParameters=GPIO_Label
PD2.GPIO_Label=PMIC__SWREG_MODE
PD2.Signal=GPIO_Output
PD3.GPIOParameters=GPIO_Label
PD3.GPIO_Label=PMIC__5VREG_EN
PD3.Signal=GPIO_Output
PF0-OSC_IN\ (PF0).GPIOParameters=GPIO_Label
PF0-OSC_IN\ (PF0).GPIO_Label=MCU__RCC_OSC_IN
PF0-OSC_IN\ (PF0).Mode=HSE-External-Oscillator
PF0-OSC_IN\ (PF0).Signal=RCC_OSC_IN
PF1-OSC_OUT\ (PF1).GPIOParameters=GPIO_Label
PF1-OSC_OUT\ (PF1).GPIO_Label=MCU__RCC_OSC_OUT
PF1-OSC_OUT\ (PF1).Mode=HSE-External-Oscillator
PF1-OSC_OUT\ (PF1).Signal=RCC_OSC_OUT
PF2-NRST.GPIOParameters=GPIO_Label
PF2-NRST.GPIO_Label=MCU__RESET__NRST
PF2-NRST.Signal=GPXTI2
RCC.HSE_VALUE=24000000
RCC.SYSCLKFreq_VALUE=64000000
RCC.SYSCLKSource=RCC_SYSCLKSOURCE_PLLCLK
board=custom

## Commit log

2026-02-23 feat: add plots
2026-02-23 feat: add production files
2026-03-01 feat: small PCB and (even smaller) schem adjustments
2026-03-05 feat: small adjustments to PCB and schem
2026-03-16 feat: many changes
2026-03-17 feat: generate schematic PDF and fix minor schematic mistakes
2026-03-22 feat: small changes in schematics, some PCB routing
2026-04-27 feat: failed PCB routing
